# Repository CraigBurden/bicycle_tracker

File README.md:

# bicycle_tracker
An open-source LoRa GPS tracker intended to be attached to a bicycle

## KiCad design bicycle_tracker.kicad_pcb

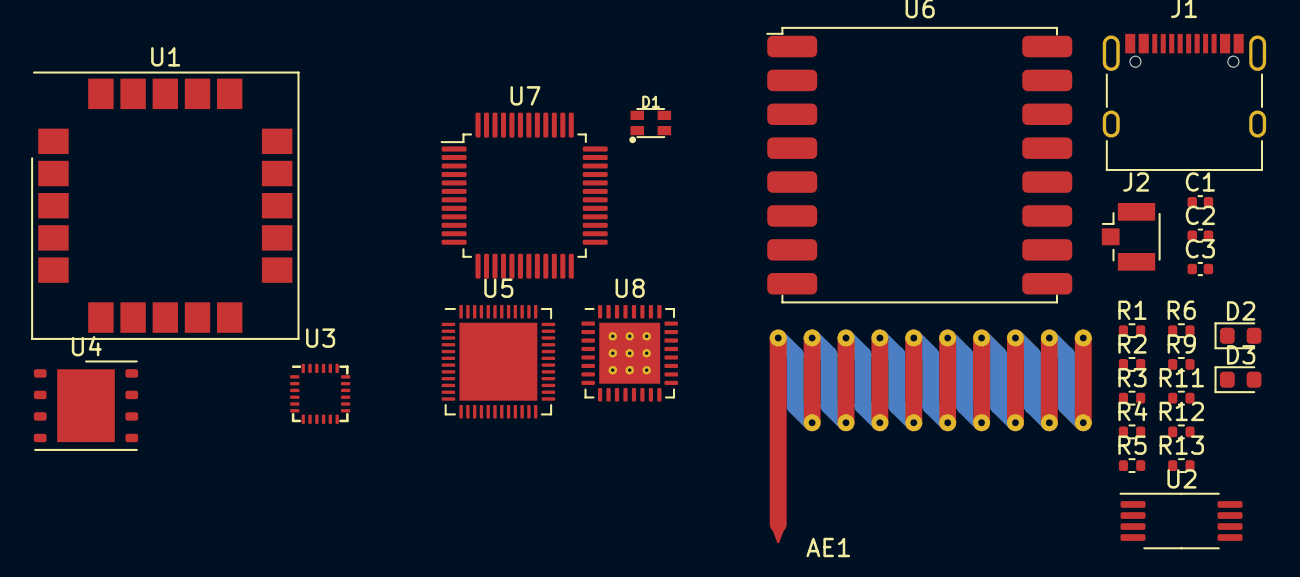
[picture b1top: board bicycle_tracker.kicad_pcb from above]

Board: 2 copper layers, 27 parts (0 on the bottom side), 26 nets, no tracks yet.

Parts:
AE1: ANT_SWRA416_RIGHT; Texas_SWRA416_868MHz_915MHz
C1: 100nF; C_0402_1005Metric
C2, C3: DNP; C_0402_1005Metric
D1: LED_RGB_0606; LED_0606
D2: RX; LED_0603_1608Metric
D3: TX; LED_0603_1608Metric
J1: USB_C_KH-TYPE-C-16P; USB_C_Receptacle_XKB_U262-16XN-4BVC11
J2: ANT; U.FL_Hirose_U.FL-R-SMT-1_Vertical
R1, R2, R3: 100R; R_0402_1005Metric
R4, R5: 5k1; R_0402_1005Metric
R6, R12, R13: 1k; R_0402_1005Metric
R9: 0R; R_0402_1005Metric
R11: 470R; R_0402_1005Metric
U1: SAM-M10Q; ublox_SAM-M8Q
U2: 24LC64; TSSOP-8_4.4x3mm_P0.65mm
U3: ICM-20948; InvenSense_QFN-24_3x3mm_P0.4mm
U4: W25Q32JVZP; WSON-8-1EP_6x5mm_P1.27mm_EP3.4x4.3mm
U5: nRF52832-QFXX; QFN-48-1EP_6x6mm_P0.4mm_EP4.6x4.6mm
U6: RFM95W-868S2; HOPERF_RFM9XW_SMD
U7: FT2232D; LQFP-48_7x7mm_P0.5mm
U8: nPM1300-QEXX; QFN-32-1EP_5x5mm_P0.5mm_EP3.6x3.6mm_ThermalVias

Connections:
+1V8: U3.8 (VDDIO), U3.9 (SDO/AD0), U3.22 (~CS)
+3V3: D1.4 (A), R6.1, U1.2 (VCC_IO), U1.17 (VCC), U2.8 (VCC), U3.13 (VDD), U6.13 (3.3V)
+5V: J1.A4 (VBUS), J1.A9 (VBUS), J1.B4 (VBUS), J1.B9 (VBUS), U7.3 (VCC), U7.42 (VCC), U7.46 (AVCC)
/3V3_OUT: R12.1, R13.1, U7.6 (3V3OUT), U7.14 (VCCIOA), U7.31 (VCCIOB)
/I2C_SCL: U1.12 (SCL), U2.6 (SCL), U3.23 (SCL/SCLK)
/I2C_SDA: U1.9 (SDA), U2.5 (SDA), U3.24 (SDA/SDI)
/SWDIO: R11.2, U7.22 (ADBUS2)
/USB_D+: J1.A6 (D+), J1.B6 (D+), U7.7 (USBDP)
/USB_D-: J1.A7 (D-), J1.B7 (D-), U7.8 (USBDM)
/VDD_SPI: C1.2, U4.8 (VCC)
GND: C1.1, C2.2, C3.2, J1.A1 (GND), J1.A12 (GND), J1.B1 (GND), J1.B12 (GND), J1.S1 (SHIELD), J2.2 (Ext), R4.2, R5.2, U1.1 (GND), U1.4 (GND), U1.5 (GND), U1.6 (GND), U1.10 (GND), U1.11 (GND), U1.15 (GND), U1.16 (GND), U1.20 (GND), U2.1 (A0), U2.2 (A1), U2.3 (A2), U2.4 (GND), U3.11 (FSYNC), U3.18 (GND), U3.20 (GND), U4.4 (GND), U4.9 (EP), U6.1 (GND), U6.8 (GND), U6.10 (GND), U7.9 (GND), U7.18 (GND), U7.25 (GND), U7.34 (GND), U7.45 (AGND)
unnamed: C3.1, R9.1
unnamed: D1.3 (BK), R3.1
unnamed: D1.2 (GK), R2.1
unnamed: D1.1 (RK), R1.1
unnamed: D2.2 (A), R13.2
unnamed: D2.1 (K), U7.28 (BCBUS2)
unnamed: D3.2 (A), R12.2
unnamed: D3.1 (K), U7.27 (BCBUS3)
unnamed: J1.A5 (CC1), R4.1
unnamed: J1.B5 (CC2), R5.1
unnamed: R6.2, U5.24 (P0.21/~RESET)
unnamed: U5.13 (VDD), U5.36 (VDD), U5.48 (VDD)
unnamed: U5.31 (VSS), U5.45 (VSS), U5.49 (VSS)
unnamed: C2.1, R9.2, U6.9 (ANT)
unnamed: R11.1, U7.23 (ADBUS1)

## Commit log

2023-11-12 Basic design
2023-11-13 Checkpoint
2024-01-05 Swapped to NRF and made a bunch of progress
